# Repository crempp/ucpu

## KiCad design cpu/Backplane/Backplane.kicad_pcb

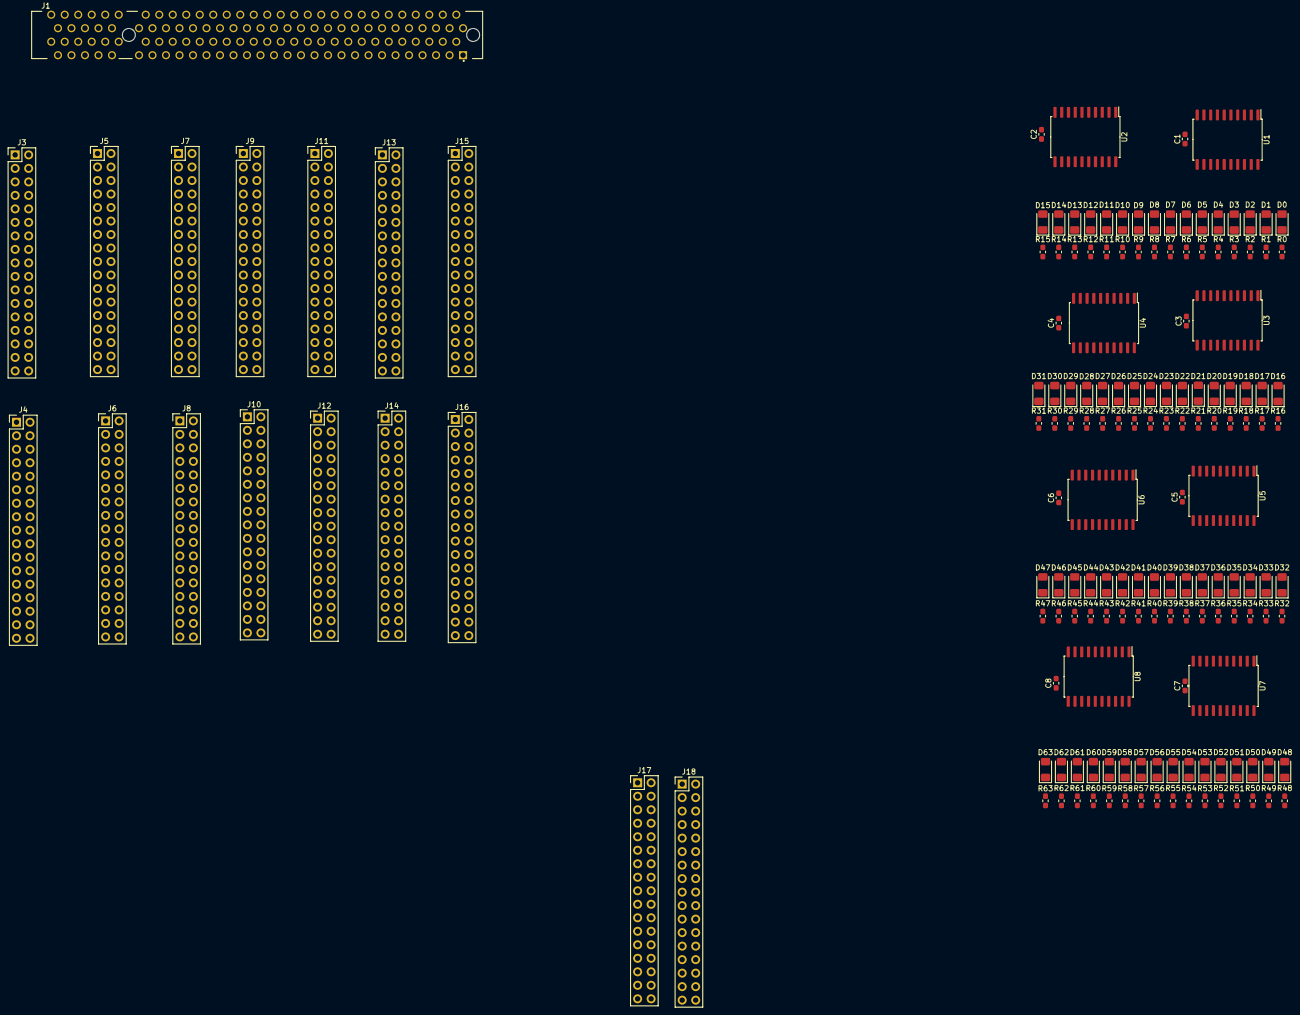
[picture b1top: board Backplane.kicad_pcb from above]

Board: 2 copper layers, 161 parts (0 on the bottom side), 226 nets, no tracks yet.

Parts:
C1, C2, C3, C4, C5, C6, C7, C8: 0.1uF; C_0603_1608Metric_Pad1.05x0.95mm_HandSolder
D0, D1, D2, D3, D4, D5, D6, D7, D8, D9, D10, D11, D12, D13, D14, D15, D16, D17, D18, D19, D20, D21, D22, D23, D24, D25, D26, D27, D28, D29, D30, D31, D32, D33, D34, D35, D36, D37, D38, D39, D40, D41, D42, D43, D44, D45, D46, D47, D48, D49, D50, D51, D52, D53, D54, D55, D56, D57, D58, D59, D60, D61, D62, D63: LED_BLUE; LED_1206_3216Metric_Pad1.42x1.75mm_HandSolder
J1: GPR_A; TE_1-5145154-2
J3: GPR B1; PinHeader_2x17_P2.54mm_Vertical
J4: GPR B2; PinHeader_2x17_P2.54mm_Vertical
J5: GPR C1; PinHeader_2x17_P2.54mm_Vertical
J6: GPR C2; PinHeader_2x17_P2.54mm_Vertical
J7: GPR D1; PinHeader_2x17_P2.54mm_Vertical
J8: GPR D2; PinHeader_2x17_P2.54mm_Vertical
J9: SI 1; PinHeader_2x17_P2.54mm_Vertical
J10: SI 2; PinHeader_2x17_P2.54mm_Vertical
J11: DI 1; PinHeader_2x17_P2.54mm_Vertical
J12: DI 2; PinHeader_2x17_P2.54mm_Vertical
J13: SP 1; PinHeader_2x17_P2.54mm_Vertical
J14: SP 2; PinHeader_2x17_P2.54mm_Vertical
J15: PC 1; PinHeader_2x17_P2.54mm_Vertical
J16: PC 2; PinHeader_2x17_P2.54mm_Vertical
J17: HOLDING 1; PinHeader_2x17_P2.54mm_Vertical
J18: HOLDING 2; PinHeader_2x17_P2.54mm_Vertical
R0, R1, R2, R3, R4, R5, R6, R7, R8, R9, R10, R11, R12, R13, R14, R15, R16, R17, R18, R19, R20, R21, R22, R23, R24, R25, R26, R27, R28, R29, R30, R31, R32, R33, R34, R35, R36, R37, R38, R39, R40, R41, R42, R43, R44, R45, R46, R47, R48, R49, R50, R51, R52, R53, R54, R55, R56, R57, R58, R59, R60, R61, R62, R63: 220R; R_0603_1608Metric_Pad1.05x0.95mm_HandSolder
U1, U2, U3, U4, U5, U6, U7, U8: 74LS245; SOIC-20W_7.5x12.8mm_P1.27mm

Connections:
+5V: C1.1, C2.1, C3.1, C4.1, C5.1, C6.1, C7.1, C8.1, J3.34, J4.34, J5.34, J6.34, J7.34, J8.34, J9.34, J10.34, J11.34, J12.34, J13.34, J14.34, J15.34, J16.34, J17.34, J18.34, U1.1, U1.20, U2.1, U2.20, U3.1, U3.20, U4.1, U4.20, U5.1, U5.20, U6.1, U6.20, U7.1, U7.20, U8.1, U8.20
/CLK: J3.31, J5.31, J7.31, J9.31, J11.31, J13.31, J15.31
/HLT: J3.27, J5.27, J7.27, J9.27, J11.27, J13.27, J15.27
/RST: J3.23, J5.23, J7.23, J9.23, J11.23, J13.23, J15.23
/a_bus_00: J10.2, J12.2, J14.2, J16.2, U7.2
/a_bus_01: J10.4, J12.4, J14.4, J16.4, U7.3
/a_bus_02: J10.6, J12.6, J14.6, J16.6, U7.4
/a_bus_03: J10.8, J12.8, J14.8, J16.8, U7.5
/a_bus_04: J10.10, J12.10, J14.10, J16.10, U7.6
/a_bus_05: J10.12, J12.12, J14.12, J16.12, U7.7
/a_bus_06: J10.14, J12.14, J14.14, J16.14, U7.8
/a_bus_07: J10.16, J12.16, J14.16, J16.16, U7.9
/a_bus_08: J10.18, J12.18, J14.18, J16.18, U8.2
/a_bus_09: J10.20, J12.20, J14.20, J16.20, U8.3
/a_bus_10: J10.22, J12.22, J14.22, J16.22, U8.4
/a_bus_11: J10.24, J12.24, J14.24, J16.24, U8.5
/a_bus_12: J10.26, J12.26, J14.26, J16.26, U8.6
/a_bus_13: J10.28, J12.28, J14.28, J16.28, U8.7
/a_bus_14: J10.30, J12.30, J14.30, J16.30, U8.8
/a_bus_15: J10.32, J12.32, J14.32, J16.32, U8.9
/a_bus_write_di: J11.5, J18.16
/a_bus_write_pc: J13.5, J15.5, J18.5, J18.15
/a_bus_write_si: J9.5, J18.6
/d_bus_00: J3.2, J5.2, J7.2, J9.2, J11.2, J13.2, J15.2, U1.2
/d_bus_01: J3.4, J5.4, J7.4, J9.4, J11.4, J13.4, J15.4, U1.3
/d_bus_02: J3.6, J5.6, J7.6, J9.6, J11.6, J13.6, J15.6, U1.4
/d_bus_03: J3.8, J5.8, J7.8, J9.8, J11.8, J13.8, J15.8, U1.5
/d_bus_04: J3.10, J5.10, J7.10, J9.10, J11.10, J13.10, J15.10, U1.6
/d_bus_05: J3.12, J5.12, J7.12, J9.12, J11.12, J13.12, J15.12, U1.7
/d_bus_06: J3.14, J5.14, J7.14, J9.14, J11.14, J13.14, J15.14, U1.8
/d_bus_07: J3.16, J5.16, J7.16, J9.16, J11.16, J13.16, J15.16, U1.9
/d_bus_08: J3.18, J5.18, J7.18, J9.18, J11.18, J13.18, J15.18, U2.2
/d_bus_09: J3.20, J5.20, J7.20, J9.20, J11.20, J13.20, J15.20, U2.3
/d_bus_10: J3.22, J5.22, J7.22, J9.22, J11.22, J13.22, J15.22, U2.4
/d_bus_11: J3.24, J5.24, J7.24, J9.24, J11.24, J13.24, J15.24, U2.5
/d_bus_12: J3.26, J5.26, J7.26, J9.26, J11.26, J13.26, J15.26, U2.6
/d_bus_13: J3.28, J5.28, J7.28, J9.28, J11.28, J13.28, J15.28, U2.7
/d_bus_14: J3.30, J5.30, J7.30, J9.30, J11.30, J13.30, J15.30, U2.8
/d_bus_15: J3.32, J5.32, J7.32, J9.32, J11.32, J13.32, J15.32, U2.9
/d_bus_read_di: J11.1, J18.12
/d_bus_read_gpr_b: J3.1, J17.10
/d_bus_read_gpr_c: J5.1, J17.18
/d_bus_read_gpr_d: J7.1, J17.26
/d_bus_read_pc: J13.1, J15.1, J18.1, J18.11
/d_bus_read_si: J9.1, J18.2
/d_bus_write_di: J11.3, J18.14
/d_bus_write_gpr_b: J3.3, J17.12
/d_bus_write_gpr_c: J5.3, J17.20
/d_bus_write_gpr_d: J7.3, J17.28
/d_bus_write_pc: J13.3, J15.3, J18.3, J18.13
/d_bus_write_si: J9.3, J18.4
/reg_dec_di: J11.9, J18.20
/reg_dec_pc: J13.9, J15.9, J18.9, J18.19
/reg_dec_si: J9.9, J18.10
/reg_inc_di: J11.7, J18.18
/reg_inc_pc: J13.7, J15.7, J18.7, J18.17
/reg_inc_si: J9.7, J18.8
/x_bus_00: J4.31, J6.31, J8.31, U3.2
/x_bus_01: J4.29, J6.29, J8.29, U3.3
/x_bus_02: J4.27, J6.27, J8.27, U3.4
/x_bus_03: J4.25, J6.25, J8.25, U3.5
/x_bus_04: J4.23, J6.23, J8.23, U3.6
/x_bus_05: J4.21, J6.21, J8.21, U3.7
/x_bus_06: J4.19, J6.19, J8.19, U3.8
/x_bus_07: J4.17, J6.17, J8.17, U3.9
/x_bus_08: J4.15, J6.15, J8.15, U4.2
/x_bus_09: J4.13, J6.13, J8.13, U4.3
/x_bus_10: J4.11, J6.11, J8.11, U4.4
/x_bus_11: J4.9, J6.9, J8.9, U4.5
/x_bus_12: J4.7, J6.7, J8.7, U4.6
/x_bus_13: J4.5, J6.5, J8.5, U4.7
/x_bus_14: J4.3, J6.3, J8.3, U4.8
/x_bus_15: J4.1, J6.1, J8.1, U4.9
/x_bus_write_gpr_b: J3.5, J17.14
/x_bus_write_gpr_c: J5.5, J17.22
/x_bus_write_gpr_d: J7.5, J17.30
/y_bus_00: J4.2, J6.2, J8.2, U5.2
/y_bus_01: J4.4, J6.4, J8.4, U5.3
/y_bus_02: J4.6, J6.6, J8.6, U5.4
/y_bus_03: J4.8, J6.8, J8.8, U5.5
/y_bus_04: J4.10, J6.10, J8.10, U5.6
/y_bus_05: J4.12, J6.12, J8.12, U5.7
/y_bus_06: J4.14, J6.14, J8.14, U5.8
/y_bus_07: J4.16, J6.16, J8.16, U5.9
/y_bus_08: J4.18, J6.18, J8.18, U6.2
/y_bus_09: J4.20, J6.20, J8.20, U6.3
/y_bus_10: J4.22, J6.22, J8.22, U6.4
/y_bus_11: J4.24, J6.24, J8.24, U6.5
/y_bus_12: J4.26, J6.26, J8.26, U6.6
/y_bus_13: J4.28, J6.28, J8.28, U6.7
/y_bus_14: J4.30, J6.30, J8.30, U6.8
/y_bus_15: J4.32, J6.32, J8.32, U6.9
/y_bus_write_gpr_b: J3.7, J17.16
/y_bus_write_gpr_c: J5.7, J17.24
/y_bus_write_gpr_d: J7.7, J17.32
/~CLK: J3.29, J5.29, J7.29, J9.29, J11.29, J13.29, J15.29
/~DBG: J3.25, J5.25, J7.25, J9.25, J11.25, J13.25, J15.25, U1.19, U2.19, U3.19, U4.19, U5.19, U6.19, U7.19, U8.19
GND: C1.2, C2.2, C3.2, C4.2, C5.2, C6.2, C7.2, C8.2, J3.33, J4.33, J5.33, J6.33, J7.33, J8.33, J9.33, J10.33, J11.33, J12.33, J13.33, J14.33, J15.33, J16.33, J17.33, J18.33, R0.2, R1.2, R2.2, R3.2, R4.2, R5.2, R6.2, R7.2, R8.2, R9.2, R10.2, R11.2, R12.2, R13.2, R14.2, R15.2, R16.2, R17.2, R18.2, R19.2, R20.2, R21.2, R22.2, R23.2, R24.2, R25.2, R26.2, R27.2, R28.2, R29.2, R30.2, R31.2, R32.2, R33.2, R34.2, R35.2, R36.2, R37.2, R38.2, R39.2, R40.2, R41.2, R42.2, R43.2, R44.2, R45.2, R46.2, R47.2, R48.2, R49.2, R50.2, R51.2, R52.2, R53.2, R54.2, R55.2, R56.2, R57.2, R58.2, R59.2, R60.2, R61.2, R62.2, R63.2, U1.10, U2.10, U3.10, U4.10, U5.10, U6.10, U7.10, U8.10
unnamed: D0.1, R0.1
unnamed: D0.2, U1.18
unnamed: D1.1, R1.1
unnamed: D1.2, U1.17
unnamed: D2.1, R2.1
unnamed: D2.2, U1.16
unnamed: D3.1, R3.1
unnamed: D3.2, U1.15
unnamed: D4.1, R4.1
unnamed: D4.2, U1.14
unnamed: D5.1, R5.1
unnamed: D5.2, U1.13
unnamed: D6.1, R6.1
unnamed: D6.2, U1.12
unnamed: D7.1, R7.1
unnamed: D7.2, U1.11
unnamed: D8.1, R8.1
unnamed: D8.2, U2.18
unnamed: D9.1, R9.1
unnamed: D9.2, U2.17
unnamed: D10.1, R10.1
unnamed: D10.2, U2.16
unnamed: D11.1, R11.1
unnamed: D11.2, U2.15
unnamed: D12.1, R12.1
unnamed: D12.2, U2.14
unnamed: D13.1, R13.1
unnamed: D13.2, U2.13
unnamed: D14.1, R14.1
unnamed: D14.2, U2.12
unnamed: D15.1, R15.1
unnamed: D15.2, U2.11
unnamed: D16.1, R16.1
unnamed: D16.2, U3.18
unnamed: D17.1, R17.1
unnamed: D17.2, U3.17
unnamed: D18.1, R18.1
unnamed: D18.2, U3.16
unnamed: D19.1, R19.1
unnamed: D19.2, U3.15
unnamed: D20.1, R20.1
unnamed: D20.2, U3.14
unnamed: D21.1, R21.1
unnamed: D21.2, U3.13
unnamed: D22.1, R22.1
unnamed: D22.2, U3.12
unnamed: D23.1, R23.1
unnamed: D23.2, U3.11
unnamed: D24.1, R24.1
unnamed: D24.2, U4.18
unnamed: D25.1, R25.1
unnamed: D25.2, U4.17
unnamed: D26.1, R26.1
unnamed: D26.2, U4.16
unnamed: D27.1, R27.1
unnamed: D27.2, U4.15
unnamed: D28.1, R28.1
unnamed: D28.2, U4.14
unnamed: D29.1, R29.1
unnamed: D29.2, U4.13
unnamed: D30.1, R30.1
unnamed: D30.2, U4.12
unnamed: D31.1, R31.1
unnamed: D31.2, U4.11
unnamed: D32.1, R32.1
unnamed: D32.2, U5.18
unnamed: D33.1, R33.1
unnamed: D33.2, U5.17
unnamed: D34.1, R34.1
unnamed: D34.2, U5.16
unnamed: D35.1, R35.1
unnamed: D35.2, U5.15
unnamed: D36.1, R36.1
unnamed: D36.2, U5.14
unnamed: D37.1, R37.1
unnamed: D37.2, U5.13
unnamed: D38.1, R38.1
unnamed: D38.2, U5.12
unnamed: D39.1, R39.1
unnamed: D39.2, U5.11
unnamed: D40.1, R40.1
unnamed: D40.2, U6.18
unnamed: D41.1, R41.1
unnamed: D41.2, U6.17
unnamed: D42.1, R42.1
unnamed: D42.2, U6.16
unnamed: D43.1, R43.1
unnamed: D43.2, U6.15
unnamed: D44.1, R44.1
unnamed: D44.2, U6.14
unnamed: D45.1, R45.1
unnamed: D45.2, U6.13
unnamed: D46.1, R46.1
unnamed: D46.2, U6.12
unnamed: D47.1, R47.1
unnamed: D47.2, U6.11
unnamed: D48.1, R48.1
unnamed: D48.2, U7.18
unnamed: D49.1, R49.1
unnamed: D49.2, U7.17
unnamed: D50.1, R50.1
unnamed: D50.2, U7.16
unnamed: D51.1, R51.1
unnamed: D51.2, U7.15
unnamed: D52.1, R52.1
unnamed: D52.2, U7.14
unnamed: D53.1, R53.1
unnamed: D53.2, U7.13
unnamed: D54.1, R54.1
unnamed: D54.2, U7.12
unnamed: D55.1, R55.1
unnamed: D55.2, U7.11
unnamed: D56.1, R56.1
unnamed: D56.2, U8.18
unnamed: D57.1, R57.1
unnamed: D57.2, U8.17
unnamed: D58.1, R58.1
unnamed: D58.2, U8.16
unnamed: D59.1, R59.1
unnamed: D59.2, U8.15
unnamed: D60.1, R60.1
unnamed: D60.2, U8.14
unnamed: D61.1, R61.1
unnamed: D61.2, U8.13
unnamed: D62.1, R62.1
unnamed: D62.2, U8.12
unnamed: D63.1, R63.1
unnamed: D63.2, U8.11

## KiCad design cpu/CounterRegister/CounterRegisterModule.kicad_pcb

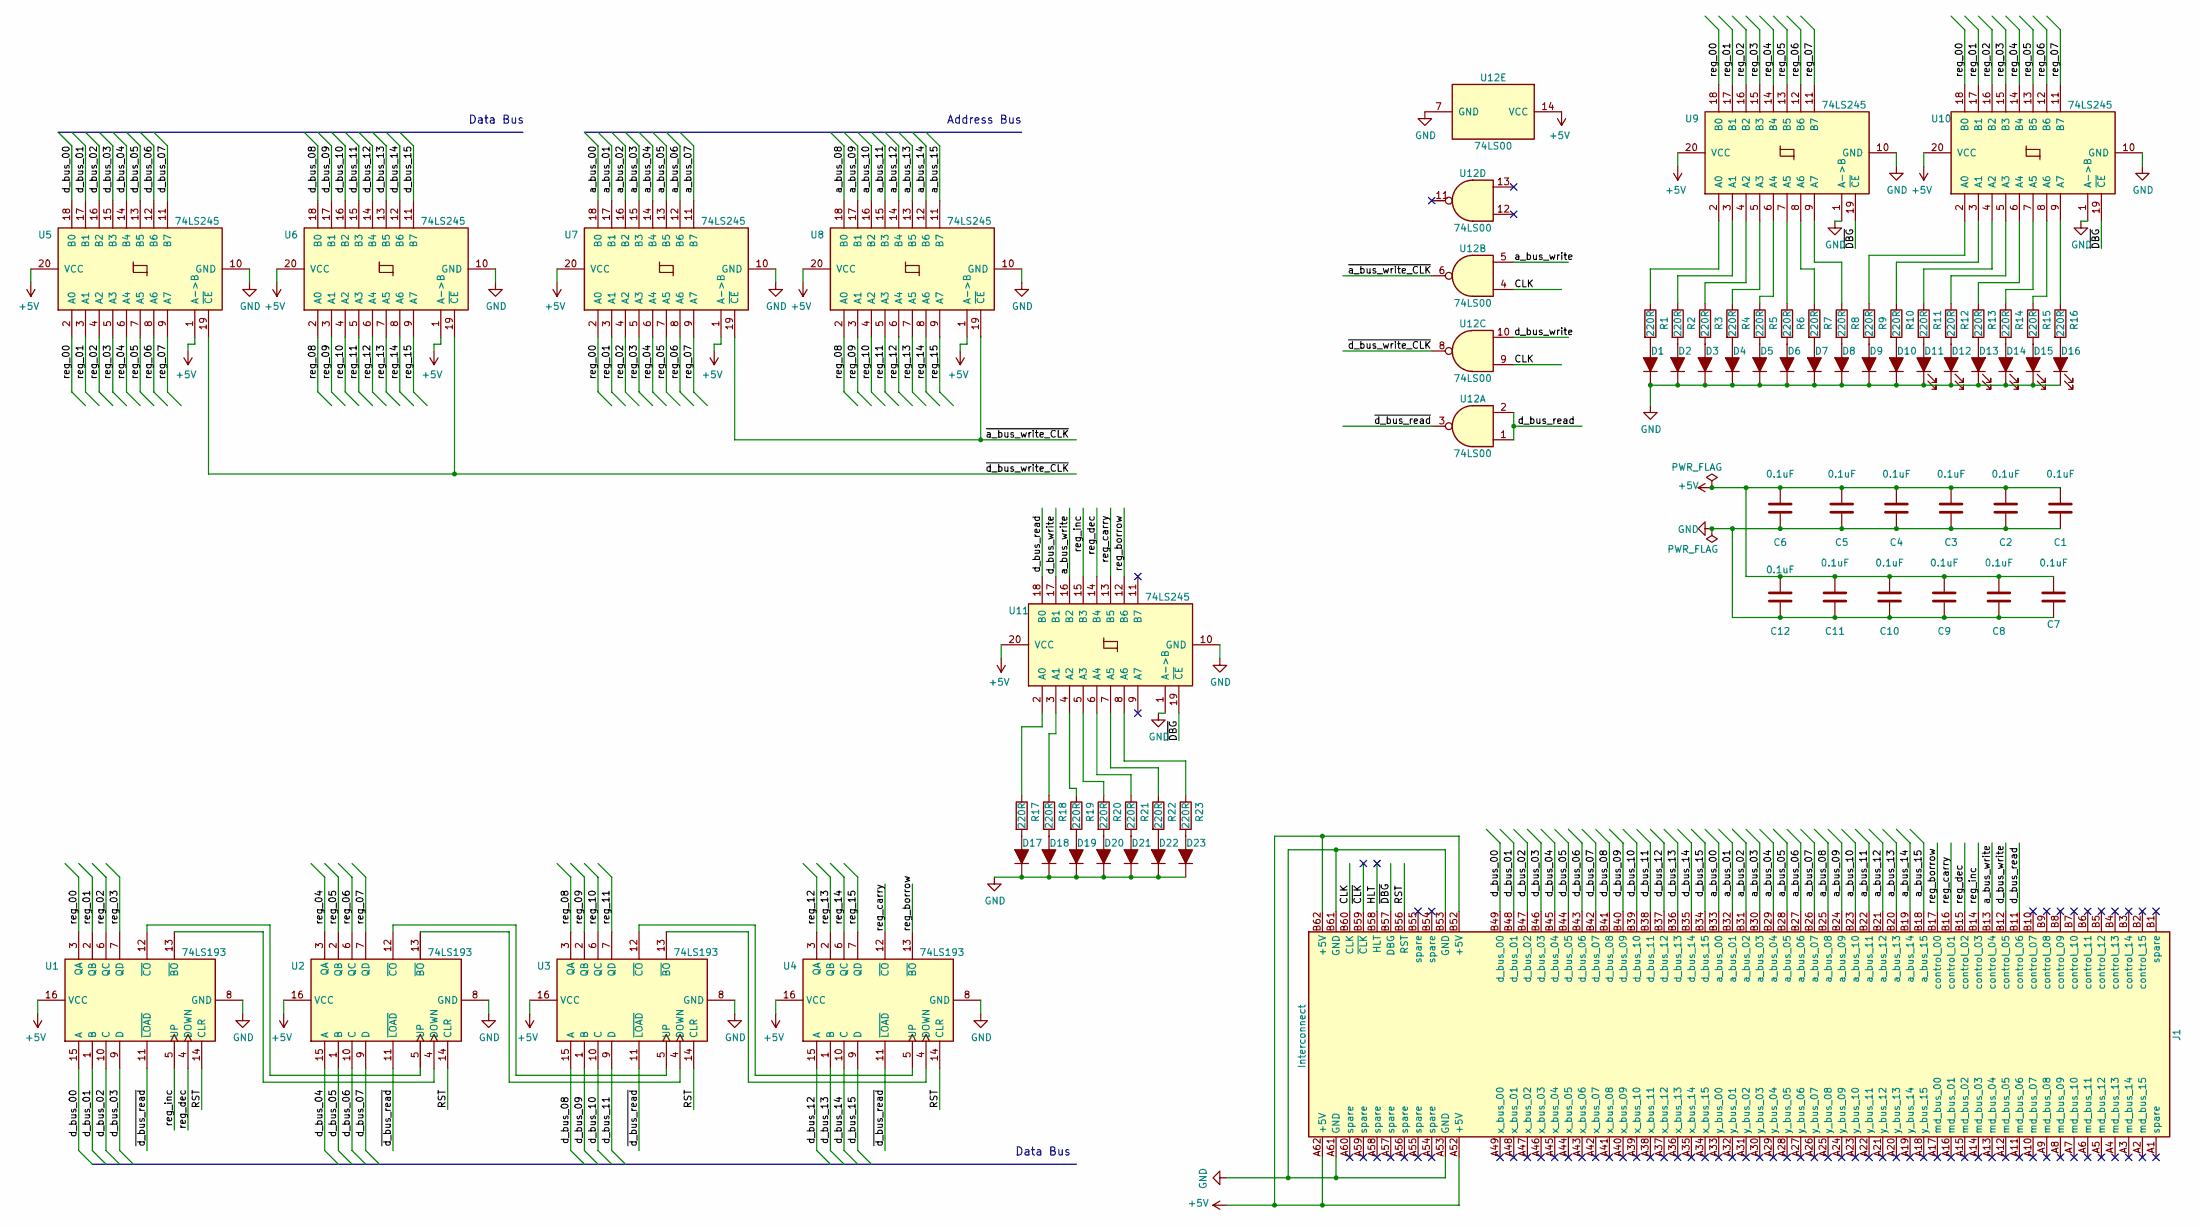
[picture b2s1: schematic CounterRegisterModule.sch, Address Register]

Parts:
C1, C2, C3, C4, C5, C6, C7, C8, C9, C10, C11, C12: 0.1uF; C_0603_1608Metric_Pad1.05x0.95mm_HandSolder; Digikey 399-1096-1-ND
D1, D2, D3, D4, D5, D6, D7, D8, D9, D10, D11, D12, D13, D14, D15, D16: D_RED; LED_1206_3216Metric_Pad1.42x1.75mm_HandSolder; Digikey 732-4978-1-ND
D17, D18, D19, D20, D21, D22, D23: D_AMBER; LED_1206_3216Metric_Pad1.42x1.75mm_HandSolder; Digikey 732-4988-1-ND
J1: Interconnect; BUS_PCI
R1, R2, R3, R4, R5, R6, R7, R8, R9, R10, R11, R12, R13, R14, R15, R16, R17, R18, R19, R20, R21, R22, R23: 220R; R_0603_1608Metric_Pad1.05x0.95mm_HandSolder; Digikey 311-220HRCT-ND
U1, U2, U3, U4: 74LS193; SOIC-16_3.9x9.9mm_P1.27mm; Digikey 1727-7973-1-ND
U5, U6, U7, U8, U9, U10, U11: 74LS245; SOIC-20W_7.5x12.8mm_P1.27mm
U12: 74LS00; SOIC-14_3.9x8.7mm_P1.27mm; Digikey 296-14860-1-ND

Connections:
+5V: C1.2, C2.2, C3.2, C4.2, C5.2, C6.2, C7.2, C8.2, C9.2, C10.2, C11.2, C12.2, J1.A52 (+5V), J1.A62 (+5V), J1.B52 (+5V), J1.B62 (+5V), U1.16 (VCC), U2.16 (VCC), U3.16 (VCC), U4.16 (VCC), U5.1 (A->B), U5.20 (VCC), U6.1 (A->B), U6.20 (VCC), U7.1 (A->B), U7.20 (VCC), U8.1 (A->B), U8.20 (VCC), U9.20 (VCC), U10.20 (VCC), U11.20 (VCC), U12.14 (VCC)
/CLK: J1.B60 (CLK), U12.4, U12.9
/HLT: J1.B58 (HLT)
/RST: J1.B56 (RST), U1.14 (CLR), U2.14 (CLR), U3.14 (CLR), U4.14 (CLR)
/a_bus_00: J1.B33 (a_bus_00), U7.18 (B0)
/a_bus_01: J1.B32 (a_bus_01), U7.17 (B1)
/a_bus_02: J1.B31 (a_bus_02), U7.16 (B2)
/a_bus_03: J1.B30 (a_bus_03), U7.15 (B3)
/a_bus_04: J1.B29 (a_bus_04), U7.14 (B4)
/a_bus_05: J1.B28 (a_bus_05), U7.13 (B5)
/a_bus_06: J1.B27 (a_bus_06), U7.12 (B6)
/a_bus_07: J1.B26 (a_bus_07), U7.11 (B7)
/a_bus_08: J1.B25 (a_bus_08), U8.18 (B0)
/a_bus_09: J1.B24 (a_bus_09), U8.17 (B1)
/a_bus_10: J1.B23 (a_bus_10), U8.16 (B2)
/a_bus_11: J1.B22 (a_bus_11), U8.15 (B3)
/a_bus_12: J1.B21 (a_bus_12), U8.14 (B4)
/a_bus_13: J1.B20 (a_bus_13), U8.13 (B5)
/a_bus_14: J1.B19 (a_bus_14), U8.12 (B6)
/a_bus_15: J1.B18 (a_bus_15), U8.11 (B7)
/a_bus_write: J1.B13 (control_04), U11.16 (B2), U12.5
/d_bus_00: J1.B49 (d_bus_00), U1.15 (A), U5.18 (B0)
/d_bus_01: J1.B48 (d_bus_01), U1.1 (B), U5.17 (B1)
/d_bus_02: J1.B47 (d_bus_02), U1.10 (C), U5.16 (B2)
/d_bus_03: J1.B46 (d_bus_03), U1.9 (D), U5.15 (B3)
/d_bus_04: J1.B45 (d_bus_04), U2.15 (A), U5.14 (B4)
/d_bus_05: J1.B44 (d_bus_05), U2.1 (B), U5.13 (B5)
/d_bus_06: J1.B43 (d_bus_06), U2.10 (C), U5.12 (B6)
/d_bus_07: J1.B42 (d_bus_07), U2.9 (D), U5.11 (B7)
/d_bus_08: J1.B41 (d_bus_08), U3.15 (A), U6.18 (B0)
/d_bus_09: J1.B40 (d_bus_09), U3.1 (B), U6.17 (B1)
/d_bus_10: J1.B39 (d_bus_10), U3.10 (C), U6.16 (B2)
/d_bus_11: J1.B38 (d_bus_11), U3.9 (D), U6.15 (B3)
/d_bus_12: J1.B37 (d_bus_12), U4.15 (A), U6.14 (B4)
/d_bus_13: J1.B36 (d_bus_13), U4.1 (B), U6.13 (B5)
/d_bus_14: J1.B35 (d_bus_14), U4.10 (C), U6.12 (B6)
/d_bus_15: J1.B34 (d_bus_15), U4.9 (D), U6.11 (B7)
/d_bus_read: J1.B11 (control_06), U11.18 (B0), U12.1, U12.2
/d_bus_write: J1.B12 (control_05), U11.17 (B1), U12.10
/reg_00: U1.3 (QA), U5.2 (A0), U7.2 (A0), U9.18 (B0), U10.18 (B0)
/reg_01: U1.2 (QB), U5.3 (A1), U7.3 (A1), U9.17 (B1), U10.17 (B1)
/reg_02: U1.6 (QC), U5.4 (A2), U7.4 (A2), U9.16 (B2), U10.16 (B2)
/reg_03: U1.7 (QD), U5.5 (A3), U7.5 (A3), U9.15 (B3), U10.15 (B3)
/reg_04: U2.3 (QA), U5.6 (A4), U7.6 (A4), U9.14 (B4), U10.14 (B4)
/reg_05: U2.2 (QB), U5.7 (A5), U7.7 (A5), U9.13 (B5), U10.13 (B5)
/reg_06: U2.6 (QC), U5.8 (A6), U7.8 (A6), U9.12 (B6), U10.12 (B6)
/reg_07: U2.7 (QD), U5.9 (A7), U7.9 (A7), U9.11 (B7), U10.11 (B7)
/reg_08: U3.3 (QA), U6.2 (A0), U8.2 (A0)
/reg_09: U3.2 (QB), U6.3 (A1), U8.3 (A1)
/reg_10: U3.6 (QC), U6.4 (A2), U8.4 (A2)
/reg_11: U3.7 (QD), U6.5 (A3), U8.5 (A3)
/reg_12: U4.3 (QA), U6.6 (A4), U8.6 (A4)
/reg_13: U4.2 (QB), U6.7 (A5), U8.7 (A5)
/reg_14: U4.6 (QC), U6.8 (A6), U8.8 (A6)
/reg_15: U4.7 (QD), U6.9 (A7), U8.9 (A7)
/reg_borrow: J1.B17 (control_00), U4.13 (~BO), U11.12 (B6)
/reg_carry: J1.B16 (control_01), U4.12 (~CO), U11.13 (B5)
/reg_dec: J1.B15 (control_02), U1.4 (DOWN), U11.14 (B4)
/reg_inc: J1.B14 (control_03), U1.5 (UP), U11.15 (B3)
/~CLK: J1.B59 (~CLK)
/~DBG: J1.B57 (DBG), U9.19 (~CE), U10.19 (~CE), U11.19 (~CE)
/~a_bus_write_CLK: U7.19 (~CE), U8.19 (~CE), U12.6
/~d_bus_read: U1.11 (~LOAD), U2.11 (~LOAD), U3.11 (~LOAD), U4.11 (~LOAD), U12.3
/~d_bus_write_CLK: U5.19 (~CE), U6.19 (~CE), U12.8
GND: C1.1, C2.1, C3.1, C4.1, C5.1, C6.1, C7.1, C8.1, C9.1, C10.1, C11.1, C12.1, D1.1 (K), D2.1 (K), D3.1 (K), D4.1 (K), D5.1 (K), D6.1 (K), D7.1 (K), D8.1 (K), D9.1 (K), D10.1 (K), D11.1 (K), D12.1 (K), D13.1 (K), D14.1 (K), D15.1 (K), D16.1 (K), D17.1 (K), D18.1 (K), D19.1 (K), D20.1 (K), D21.1 (K), D22.1 (K), D23.1 (K), J1.A53 (GND), J1.A61 (GND), J1.B53 (GND), J1.B61 (GND), U1.8 (GND), U2.8 (GND), U3.8 (GND), U4.8 (GND), U5.10 (GND), U6.10 (GND), U7.10 (GND), U8.10 (GND), U9.1 (A->B), U9.10 (GND), U10.1 (A->B), U10.10 (GND), U11.1 (A->B), U11.10 (GND), U12.7 (GND)
unnamed: D1.2 (A), R1.2
unnamed: D2.2 (A), R2.2
unnamed: D3.2 (A), R3.2
unnamed: D4.2 (A), R4.2
unnamed: D5.2 (A), R5.2
unnamed: D6.2 (A), R6.2
unnamed: D7.2 (A), R7.2
unnamed: D8.2 (A), R8.2
unnamed: D9.2 (A), R9.2
unnamed: D10.2 (A), R10.2
unnamed: D11.2 (A), R11.2
unnamed: D12.2 (A), R12.2
unnamed: D13.2 (A), R13.2
unnamed: D14.2 (A), R14.2
unnamed: D15.2 (A), R15.2
unnamed: D16.2 (A), R16.2
unnamed: D17.2 (A), R17.2
unnamed: D18.2 (A), R18.2
unnamed: D19.2 (A), R19.2
unnamed: D20.2 (A), R20.2
unnamed: D21.2 (A), R21.2
unnamed: D22.2 (A), R22.2
unnamed: D23.2 (A), R23.2
unnamed: R1.1, U9.2 (A0)
unnamed: R2.1, U9.3 (A1)
unnamed: R3.1, U9.4 (A2)
unnamed: R4.1, U9.5 (A3)
unnamed: R5.1, U9.6 (A4)
unnamed: R6.1, U9.7 (A5)
unnamed: R7.1, U9.8 (A6)
unnamed: R8.1, U9.9 (A7)
unnamed: R9.1, U10.2 (A0)
unnamed: R10.1, U10.3 (A1)
unnamed: R11.1, U10.4 (A2)
unnamed: R12.1, U10.5 (A3)
unnamed: R13.1, U10.6 (A4)
unnamed: R14.1, U10.7 (A5)
unnamed: R15.1, U10.8 (A6)
unnamed: R16.1, U10.9 (A7)
unnamed: R17.1, U11.2 (A0)
unnamed: R18.1, U11.3 (A1)
unnamed: R19.1, U11.4 (A2)
unnamed: R20.1, U11.5 (A3)
unnamed: R21.1, U11.6 (A4)
unnamed: R22.1, U11.7 (A5)
unnamed: R23.1, U11.8 (A6)
unnamed: U1.12 (~CO), U2.5 (UP)
unnamed: U1.13 (~BO), U2.4 (DOWN)
unnamed: U2.12 (~CO), U3.5 (UP)
unnamed: U2.13 (~BO), U3.4 (DOWN)
unnamed: U3.12 (~CO), U4.5 (UP)
unnamed: U3.13 (~BO), U4.4 (DOWN)

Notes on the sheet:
Data Bus
Address Bus

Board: 2 copper layers, 71 parts (0 on the bottom side), 115 nets, no tracks yet.
